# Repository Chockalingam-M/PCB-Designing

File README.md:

# PCB-Designing

🚀 Designed and developed this PCB as a demonstration of my skills in hardware design and precision layout. From component placement to trace optimization, every part of this board reflects my commitment to clean, functional, and professional electronic design.

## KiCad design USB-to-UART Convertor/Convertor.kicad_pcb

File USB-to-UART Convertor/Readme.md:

Overview
This project is a USB to UART bridge designed using the CH340K USB to Serial chip. It allows for easy communication between a computer and a microcontroller through a Type-C USB connector. 
Ideal for programming or debugging microcontrollers like ESP32, STM32, etc.

This USB to UART PCB was designed by carefully following Ampnics’ video and analyzing each functional block. While the current routing can be optimized further, 
The design serves its purpose effectively. Future revisions will focus on refining the layout, improving signal integrity, and enhancing grounding practices.

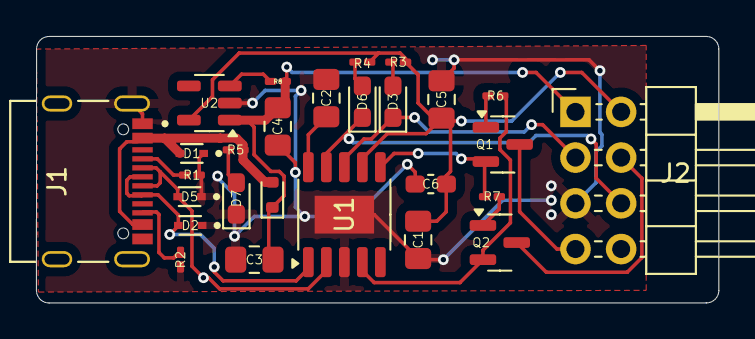
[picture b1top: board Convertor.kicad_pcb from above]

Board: 2 copper layers, 37.9 x 14.8 mm, 27 parts (0 on the bottom side), 21 nets.

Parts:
C1, C2: 100n; C_0805_2012Metric_Pad1.18x1.45mm_HandSolder
C3, C4, C5: 10u; C_0805_2012Metric_Pad1.18x1.45mm_HandSolder
C6: 0.1u; C_0603_1608Metric_Pad1.08x0.95mm_HandSolder
D1, D2, D5: LESD5D5.0CT1G; TVS_LESD5D5.0CT1G
D3, D6, D7: LED; LED_0603_1608Metric_Pad1.05x0.95mm_HandSolder
D4: D_Schottky; D_SOD-523
J1: USB_C_Receptacle_USB2.0_16P; HRO_TYPE-C-31-M-12
J2: Conn_02x04_Top_Bottom; PinHeader_2x04_P2.54mm_Horizontal
Q1, Q2: SS8050; SOT-23
R1, R2: 5.1k; R_0201_0603Metric_Pad0.64x0.40mm_HandSolder
R3, R4, R5: 220; R_0201_0603Metric_Pad0.64x0.40mm_HandSolder
R6, R7: 10k; R_0201_0603Metric_Pad0.64x0.40mm_HandSolder
R8: 100k; R_0201_0603Metric_Pad0.64x0.40mm_HandSolder
U1: CH340K; SSOP-10-1EP_3.9x4.9mm_P1mm_EP2.1x3.3mm
U2: AP2112K-3.3; SOT-23-5

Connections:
+3.3V: C1.1, C5.1, C6.1, J2.2, R3.1, R4.1, U1.7 (VCC), U2.5 (VOUT)
+5V: C3.1, C4.1, D4.1 (K), J2.1, R8.1, U2.1 (VIN)
D+: D2.2, J1.A6 (D+), J1.B6 (D+), U1.1 (UD+)
D-: D5.2, J1.A7 (D-), J1.B7 (D-), U1.2 (UD-)
DTR: Q2.2 (E), R6.1, U1.4 (~DTR)
EN: J2.7, Q1.3 (C)
GND: C1.2, C2.1, C3.2, C4.2, C5.2, C6.2, D1.1, D2.1, D5.1, D7.1 (K), J1.A12, J1.B12, J1.S1 (SHIELD), J2.5, R1.2, R2.2, U1.3 (GND), U1.11 (GND), U2.2 (GND)
IO0: J2.4, Q2.3 (C)
unnamed: D3.2 (A), R3.2
unnamed: D6.2 (A), R4.2
unnamed: D7.2 (A), R5.2
unnamed: J1.A5 (CC1), R1.1
unnamed: J1.B5 (CC2), R2.1
unnamed: Q1.1 (B), R6.2
unnamed: Q2.1 (B), R7.2
unnamed: C2.2, U1.10 (V3)
unnamed: R8.2, U2.3 (EN)
RTS: Q1.2 (E), R7.1, U1.6 (~RTS)
RXD: D3.1 (K), J2.3, U1.8 (TXD)
TXD: D6.1 (K), J2.6, U1.9 (RXD)
VBUS: D1.2, D4.2 (A), J1.A9, J1.B9, R5.1

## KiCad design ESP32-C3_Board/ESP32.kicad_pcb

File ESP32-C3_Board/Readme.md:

I’ve designed a PCB for the ESP32-C3 as my first hands-on attempt at circuit design using KiCad. This project helped me understand the complete workflow — from schematic creation to PCB layout. I followed along with a YouTube tutorial to guide the process and deepen my understanding of component placement, routing, and design rules.

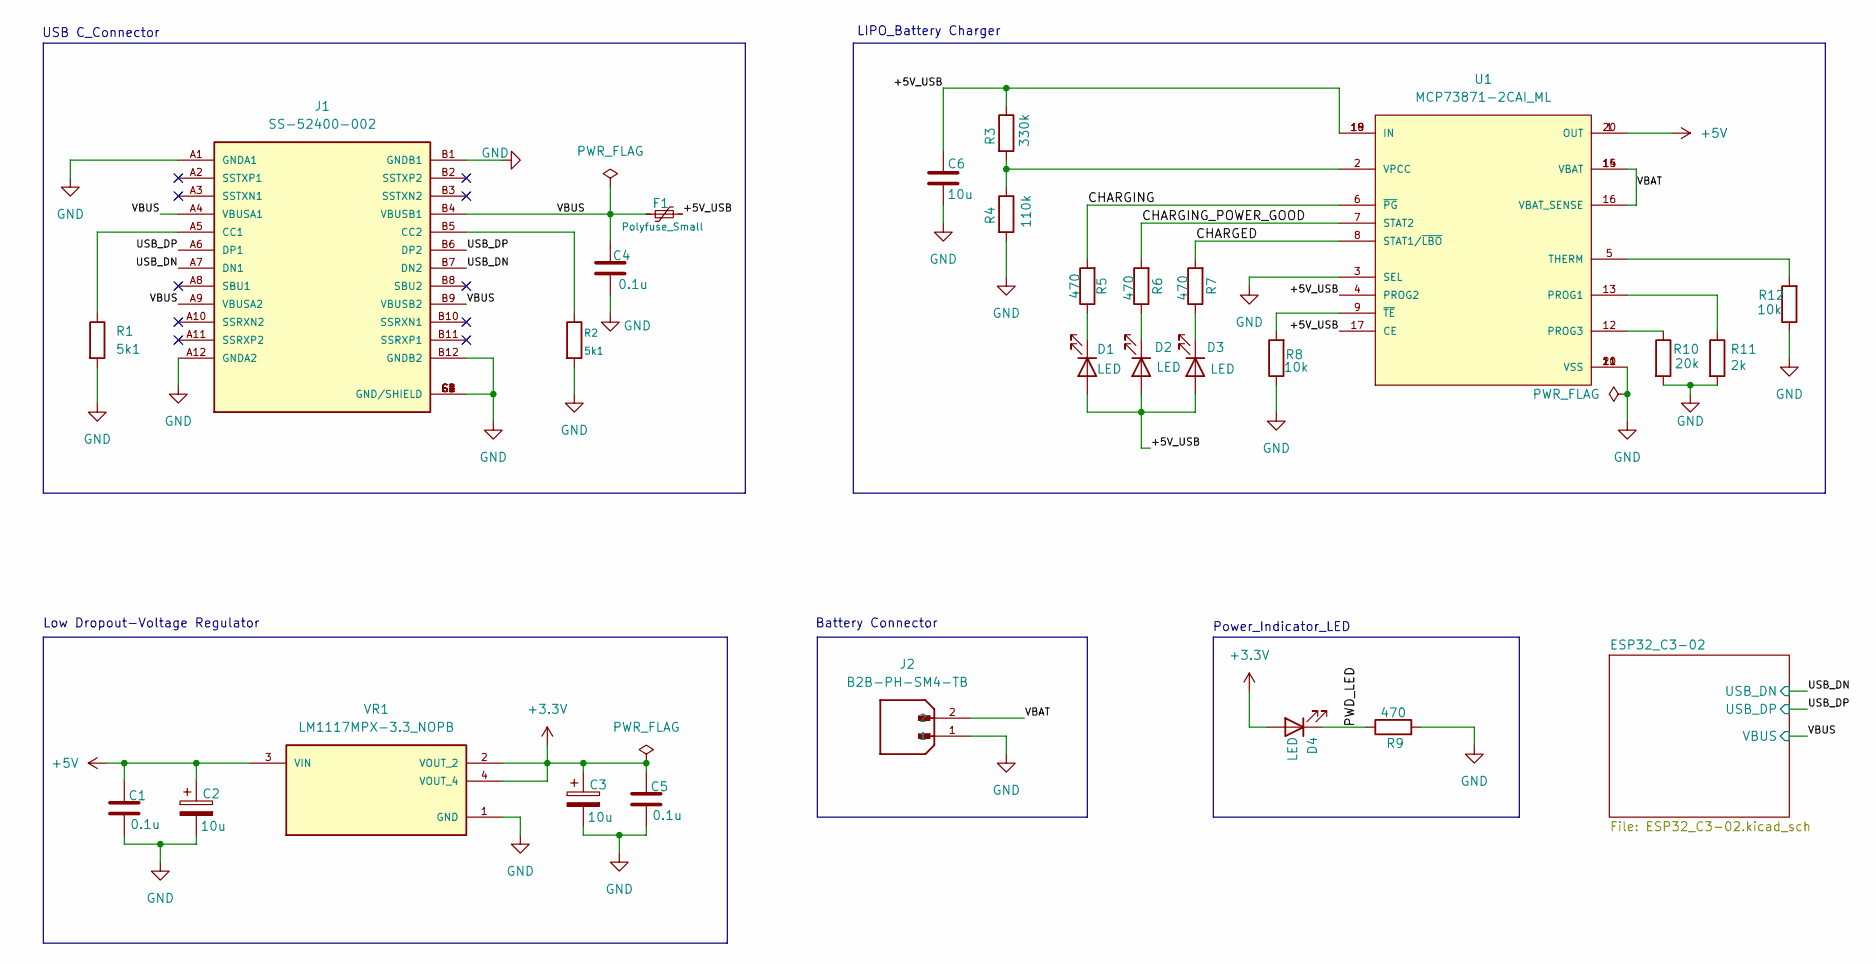
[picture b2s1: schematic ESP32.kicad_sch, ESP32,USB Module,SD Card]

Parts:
C1, C4, C5: 0.1u; C_0805_2012Metric
C2, C3, C6: 10u; CAPMP3216X180N
D1, D2, D3, D4: LED; LED_0805_2012Metric
F1: Polyfuse_Small; Fuse_0805_2012Metric
J1: SS-52400-002; BELFUSE_SS-52400-002; PARTREV A0
J2: B2B-PH-SM4-TB; JST_B2B-PH-SM4-TB; PARTREV N/A
R1, R2: 5k1; R_0805_2012Metric
R3: 330k; R_0805_2012Metric
R4: 110k; R_0805_2012Metric
R5, R6, R7, R9: 470; R_0805_2012Metric
R8, R12: 10k; R_0805_2012Metric
R10: 20k; R_0805_2012Metric
R11: 2k; R_0805_2012Metric
U1: MCP73871-2CAI_ML; QFN50P400X400X100-21N; PARTREV D
VR1: LM1117MPX-3.3_NOPB; VREG_LM1117MPX-3.3_NOPB; PARTREV O; DigiKey_Part_Number 488-LM1117MPX-33NOPBTR-ND

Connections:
+3.3V: C3.1, C5.1, D4.2 (A), VR1.2 (VOUT_2), VR1.4 (VOUT_4); also elsewhere on the board
+5V: C1.1, C2.1, U1.1 (OUT), U1.20 (OUT), VR1.3 (VIN)
/+5V_USB: C6.1, D1.2 (A), D2.2 (A), D3.2 (A), F1.2, R3.1, U1.4 (PROG2), U1.17 (CE), U1.18 (IN), U1.19 (IN)
/CHARGED: R7.2, U1.8 (STAT1/~LBO)
/CHARGING: R5.2, U1.6 (~PG)
/CHARGING_POWER_GOOD: R6.2, U1.7 (STAT2)
/PWD_LED: D4.1 (K), R9.1
/USB_DN: J1.A7 (DN1), J1.B7 (DN2); also elsewhere on the board
/USB_DP: J1.A6 (DP1), J1.B6 (DP2); also elsewhere on the board
/VBAT: J2.2, U1.14 (VBAT), U1.15 (VBAT), U1.16 (VBAT_SENSE)
/VBUS: C4.1, F1.1, J1.A4 (VBUSA1), J1.A9 (VBUSA2), J1.B4 (VBUSB1), J1.B9 (VBUSB2); also elsewhere on the board
GND: C1.2, C2.2, C3.2, C4.2, C5.2, C6.2, J1.A1 (GNDA1), J1.A12 (GNDA2), J1.B1 (GNDB1), J1.B12 (GNDB2), J1.G1 (GND/SHIELD), J1.G2 (GND/SHIELD), J1.G3 (GND/SHIELD), J1.G4 (GND/SHIELD), J1.S1 (GND/SHIELD), J1.S2 (GND/SHIELD), J1.S3 (GND/SHIELD), J1.S4 (GND/SHIELD), J2.1, R1.2, R2.2, R4.2, R8.1, R9.2, R10.2, R11.2, R12.1, U1.3 (SEL), U1.10 (VSS), U1.11 (VSS), U1.21 (VSS), VR1.1 (GND); also elsewhere on the board
unnamed: D1.1 (K), R5.1
unnamed: D2.1 (K), R6.1
unnamed: D3.1 (K), R7.1
unnamed: J1.A5 (CC1), R1.1
unnamed: J1.B5 (CC2), R2.1
unnamed: R11.1, U1.13 (PROG1)
unnamed: R10.1, U1.12 (PROG3)
unnamed: R12.2, U1.5 (THERM)
unnamed: R3.2, R4.1, U1.2 (VPCC)
unnamed: R8.2, U1.9 (~TE)

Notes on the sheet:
Low Dropout-Voltage Regulator
Battery Connector
Power_Indicator_LED
USB C_Connector
LIPO_Battery Charger

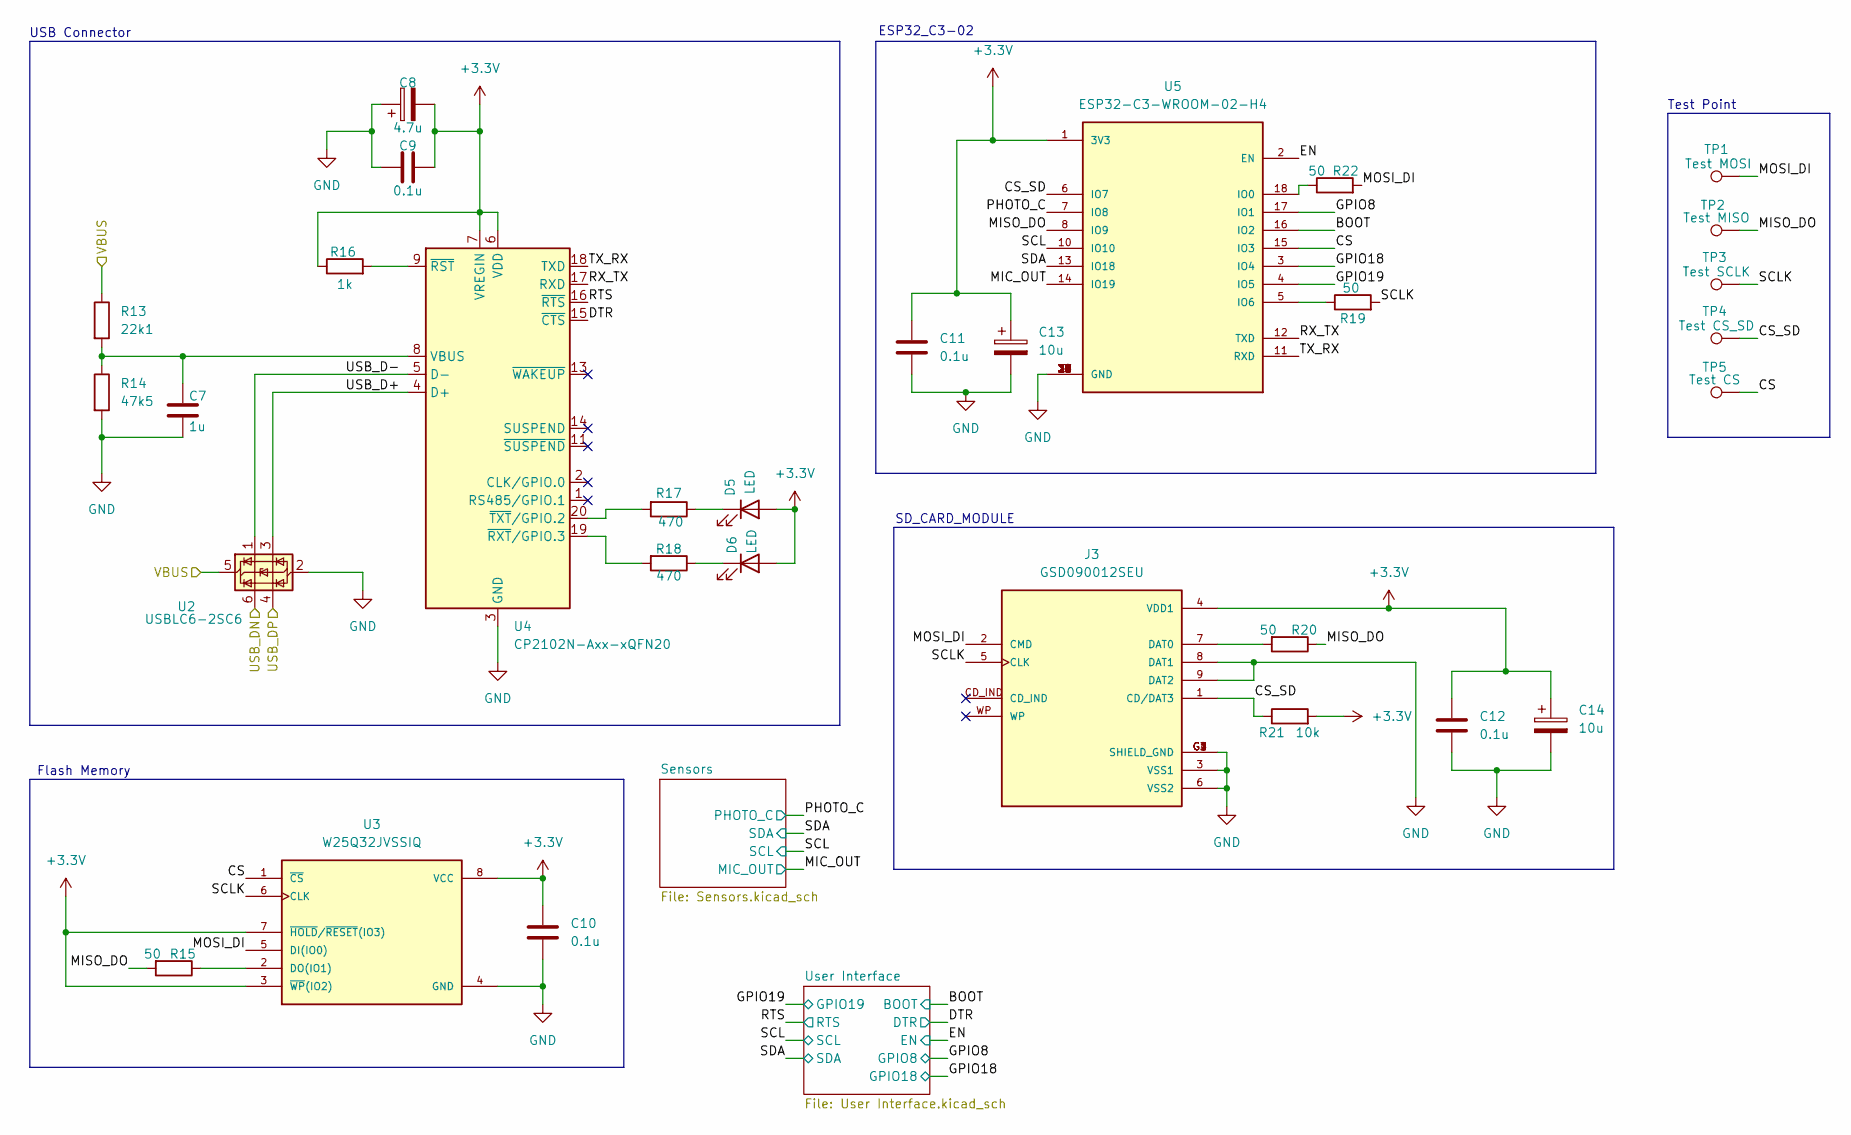
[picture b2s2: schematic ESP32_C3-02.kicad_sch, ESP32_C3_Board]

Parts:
C7: 1u; C_0805_2012Metric
C8: 4.7u; CAPMP3216X180N
C9, C10, C11, C12: 0.1u; C_0805_2012Metric
C13, C14: 10u; CAPMP3216X180N
D5, D6: LED; LED_0805_2012Metric
J3: GSD090012SEU; AMPHENOL_GSD090012SEU; PARTREV E
R13: 22k1; R_0805_2012Metric
R14: 47k5; R_0805_2012Metric
R15, R19, R20, R22: 50; R_0805_2012Metric
R16: 1k; R_0805_2012Metric
R17, R18: 470; R_0805_2012Metric
R21: 10k; R_0805_2012Metric
TP1: Test MOSI; TestPoint_Pad_D1.0mm
TP2: Test MISO; TestPoint_Pad_D1.0mm
TP3: Test SCLK; TestPoint_Pad_D1.0mm
TP4: Test CS_SD; TestPoint_Pad_D1.0mm
TP5: Test CS; TestPoint_Pad_D1.0mm
U2: USBLC6-2SC6; SOT-23-6
U3: W25Q32JVSSIQ; SOIC127P790X216-8N; M_PART_NUMBER W25QXX
U4: CP2102N-Axx-xQFN20; QFN50P400X400X100-21N
U5: ESP32-C3-WROOM-02-H4; MODULE_ESP32-C3-WROOM-02-H4

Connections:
+3.3V: C8.2, C9.2, C10.1, C11.1, C12.1, C13.1, C14.1, D5.2 (A), D6.2 (A), J3.4 (VDD1), R16.1, R21.2, U3.3 (~WP(IO2)), U3.7 (~HOLD/~RESET(IO3)), U3.8 (VCC), U4.6 (VDD), U4.7 (VREGIN), U5.1 (3V3); also elsewhere on the board
/ESP32_C3-02/BOOT: U5.16 (IO2); also elsewhere on the board
/ESP32_C3-02/CS: TP5.1, U3.1 (~CS), U5.15 (IO3)
/ESP32_C3-02/CS_SD: J3.1 (CD/DAT3), R21.1, TP4.1, U5.6 (IO7)
/ESP32_C3-02/DTR: U4.15 (~CTS); also elsewhere on the board
/ESP32_C3-02/EN: U5.2 (EN); also elsewhere on the board
/ESP32_C3-02/GPIO8: U5.17 (IO1); also elsewhere on the board
/ESP32_C3-02/GPIO18: U5.3 (IO4); also elsewhere on the board
/ESP32_C3-02/GPIO19: U5.4 (IO5); also elsewhere on the board
/ESP32_C3-02/MIC_OUT: U5.14 (IO19); also elsewhere on the board
/ESP32_C3-02/MISO_DO: R15.2, R20.1, TP2.1, U5.8 (IO9)
/ESP32_C3-02/MOSI_DI: J3.2 (CMD), R22.2, TP1.1, U3.5 (DI(IO0))
/ESP32_C3-02/PHOTO_C: U5.7 (IO8); also elsewhere on the board
/ESP32_C3-02/RTS: U4.16 (~RTS); also elsewhere on the board
/ESP32_C3-02/RX_TX: U4.17 (RXD), U5.12 (TXD)
/ESP32_C3-02/SCL: U5.10 (IO10); also elsewhere on the board
/ESP32_C3-02/SCLK: J3.5 (CLK), R19.2, TP3.1, U3.6 (CLK)
/ESP32_C3-02/SDA: U5.13 (IO18); also elsewhere on the board
/ESP32_C3-02/TX_RX: U4.18 (TXD), U5.11 (RXD)
/ESP32_C3-02/USB_D+: U2.3 (I/O2), U4.4 (D+)
/ESP32_C3-02/USB_D-: U2.1 (I/O1), U4.5 (D-)
/USB_DN: U2.6 (I/O1); also elsewhere on the board
/USB_DP: U2.4 (I/O2); also elsewhere on the board
/VBUS: R13.1, U2.5 (VBUS); also elsewhere on the board
GND: C7.2, C8.1, C9.1, C10.2, C11.2, C12.2, C13.2, C14.2, J3.3 (VSS1), J3.6 (VSS2), J3.8 (DAT1), J3.9 (DAT2), J3.G1 (SHIELD_GND), J3.G2 (SHIELD_GND), J3.G3 (SHIELD_GND), J3.G4 (SHIELD_GND), R14.2, U2.2 (GND), U3.4 (GND), U4.3 (GND), U4.12 (GND), U4.21 (GND), U5.9 (GND), U5.19 (GND), U5.20 (GND), U5.21 (GND), U5.22 (GND), U5.23 (GND), U5.24 (GND), U5.25 (GND), U5.26 (GND), U5.27 (GND), U5.28 (GND), U5.29 (GND), U5.30 (GND), U5.31 (GND), U5.32 (GND), U5.33 (GND), U5.34 (GND), U5.35 (GND), U5.36 (GND), U5.37 (GND), U5.38 (GND), U5.39 (GND); also elsewhere on the board
unnamed: D5.1 (K), R17.1
unnamed: D6.1 (K), R18.1
unnamed: J3.7 (DAT0), R20.2
unnamed: R15.1, U3.2 (DO(IO1))
unnamed: C7.1, R13.2, R14.1, U4.8 (VBUS)
unnamed: R16.2, U4.9 (~RST)
unnamed: R18.2, U4.19 (~RXT/GPIO.3)
unnamed: R17.2, U4.20 (~TXT/GPIO.2)
unnamed: R22.1, U5.18 (IO0)
unnamed: R19.1, U5.5 (IO6)

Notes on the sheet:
ESP32_C3-02
SD_CARD_MODULE
Test Point
USB Connector
Flash Memory

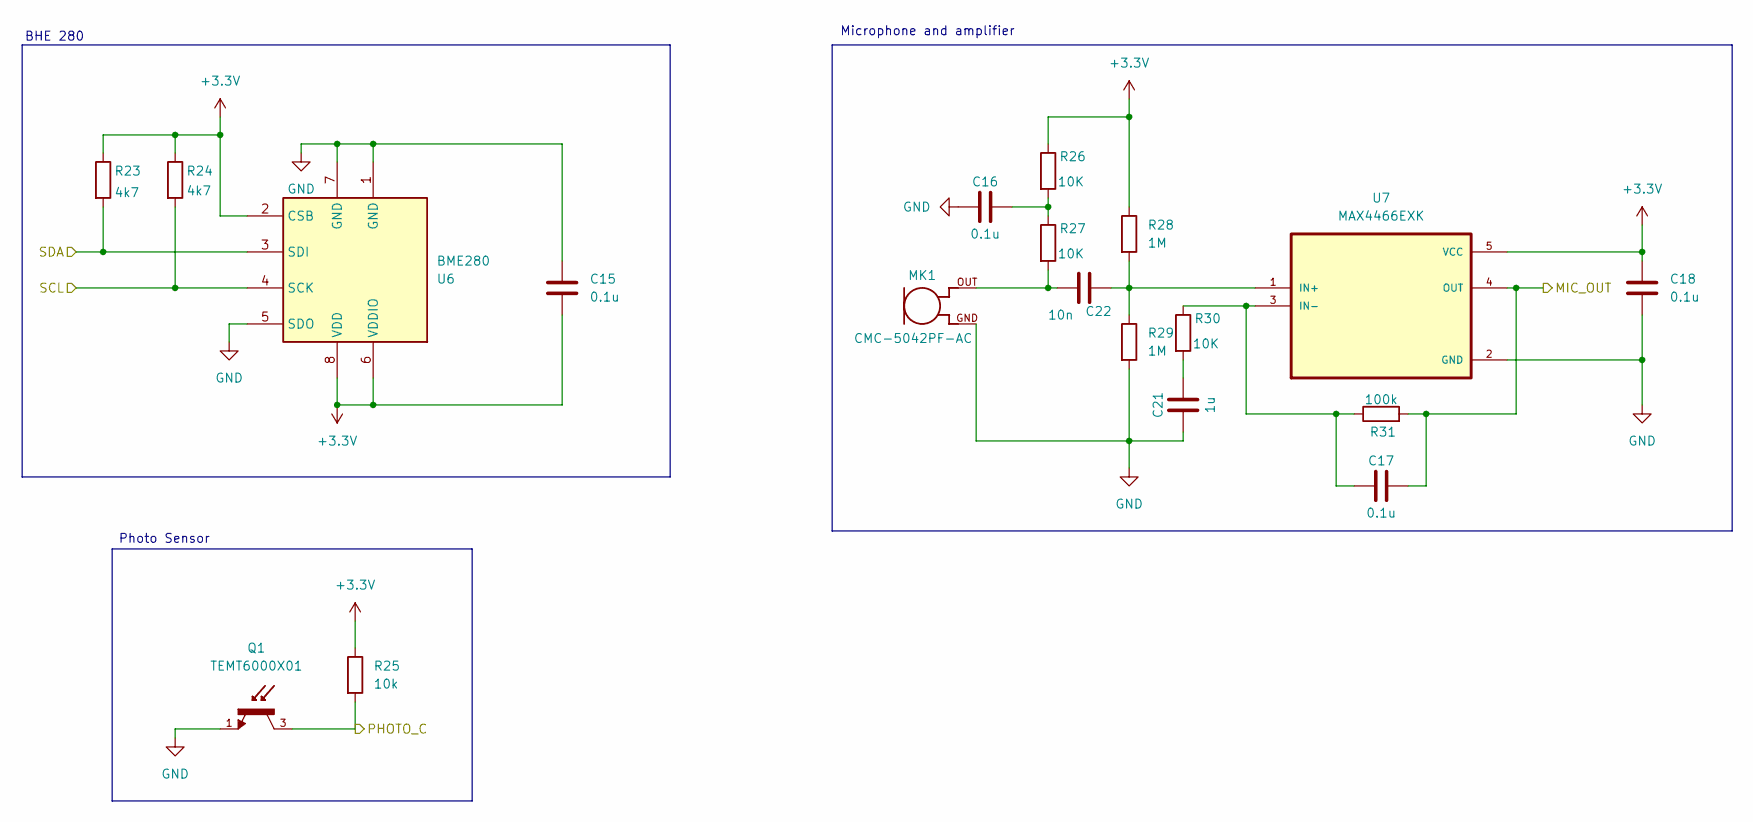
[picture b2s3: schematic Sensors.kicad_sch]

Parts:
C15, C16, C17, C18: 0.1u; C_0805_2012Metric
C21: 1u; C_0805_2012Metric
C22: 10n; C_0805_2012Metric
MK1: CMC-5042PF-AC; CUI_CMC-5042PF-AC
Q1: TEMT6000X01; TRANS_TEMT6000X01; PARTREV 1.9; DigiKey_Part_Number 751-1055-2-ND
R23, R24: 4k7; R_0805_2012Metric
R25: 10k; R_0805_2012Metric
R26, R27, R30: 10K; R_0805_2012Metric
R28, R29: 1M; R_0805_2012Metric
R31: 100k; R_0805_2012Metric
U6: BME280; Bosch_LGA-8_3x3mm_P0.8mm_ClockwisePinNumbering
U7: MAX4466EXK; SOT65P210X110-5N

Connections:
+3.3V: C15.2, C18.1, R23.1, R24.1, R25.1, R26.1, R28.1, U6.2 (CSB), U6.6 (VDDIO), U6.8 (VDD), U7.5 (VCC); also elsewhere on the board
/ESP32_C3-02/MIC_OUT: C17.2, R31.2, U7.4 (OUT); also elsewhere on the board
/ESP32_C3-02/PHOTO_C: Q1.3, R25.2; also elsewhere on the board
/ESP32_C3-02/SCL: R24.2, U6.4 (SCK); also elsewhere on the board
/ESP32_C3-02/SDA: R23.2, U6.3 (SDI); also elsewhere on the board
GND: C15.1, C16.1, C18.2, C21.1, MK1.GND, Q1.1, R29.2, U6.1 (GND), U6.5 (SDO), U6.7 (GND), U7.2 (GND); also elsewhere on the board
unnamed: C16.2, R26.2, R27.1
unnamed: C21.2, R30.2
unnamed: C22.2, MK1.OUT, R27.2
unnamed: C22.1, R28.2, R29.1, U7.1 (IN+)
unnamed: C17.1, R30.1, R31.1, U7.3 (IN-)

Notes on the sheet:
Microphone and amplifier
Photo Sensor
BHE 280

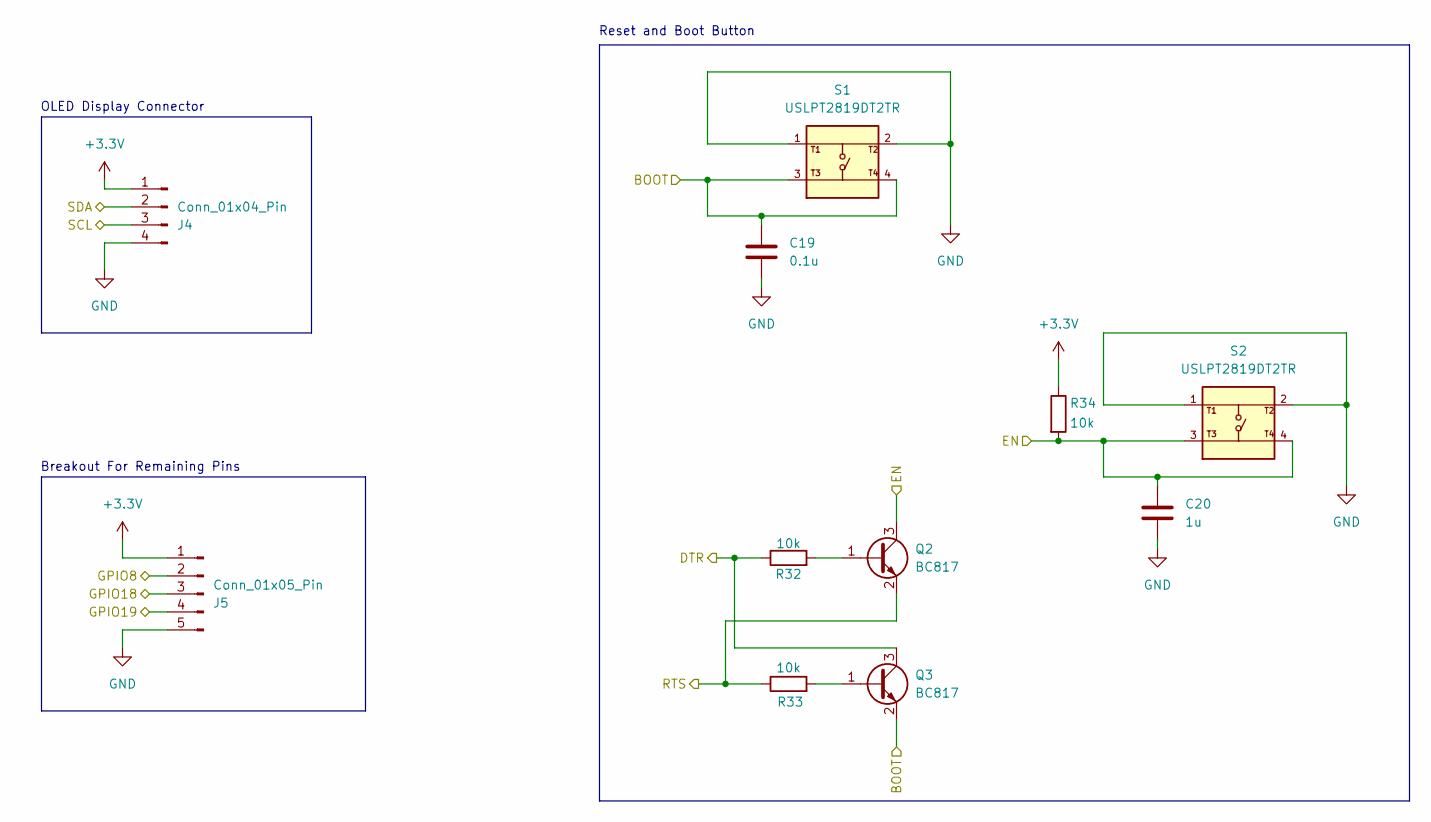
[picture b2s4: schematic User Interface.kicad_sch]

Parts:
C19: 0.1u; C_0805_2012Metric
C20: 1u; C_0805_2012Metric
J4: Conn_01x04_Pin; PinHeader_1x04_P2.54mm_Vertical
J5: Conn_01x05_Pin; PinHeader_1x05_P2.54mm_Vertical
Q2, Q3: BC817; SOT-23
R32, R33, R34: 10k; R_0805_2012Metric
S1, S2: USLPT2819DT2TR; SW_USLPT2819DT2TR; PARTREV P; DigiKey_Part_Number 450-3358-2-ND

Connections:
+3.3V: J4.1, J5.1, R34.1; also elsewhere on the board
/ESP32_C3-02/BOOT: C19.1, Q3.2 (E), S1.3, S1.4; also elsewhere on the board
/ESP32_C3-02/DTR: Q3.3 (C), R32.1; also elsewhere on the board
/ESP32_C3-02/EN: C20.1, Q2.3 (C), R34.2, S2.3, S2.4; also elsewhere on the board
/ESP32_C3-02/GPIO8: J5.2; also elsewhere on the board
/ESP32_C3-02/GPIO18: J5.3; also elsewhere on the board
/ESP32_C3-02/GPIO19: J5.4; also elsewhere on the board
/ESP32_C3-02/RTS: Q2.2 (E), R33.1; also elsewhere on the board
/ESP32_C3-02/SCL: J4.3; also elsewhere on the board
/ESP32_C3-02/SDA: J4.2; also elsewhere on the board
GND: C19.2, C20.2, J4.4, J5.5, S1.1, S1.2, S2.1, S2.2; also elsewhere on the board
unnamed: Q2.1 (B), R32.2
unnamed: Q3.1 (B), R33.2

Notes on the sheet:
Reset and Boot Button
Breakout For Remaining Pins
OLED Display Connector

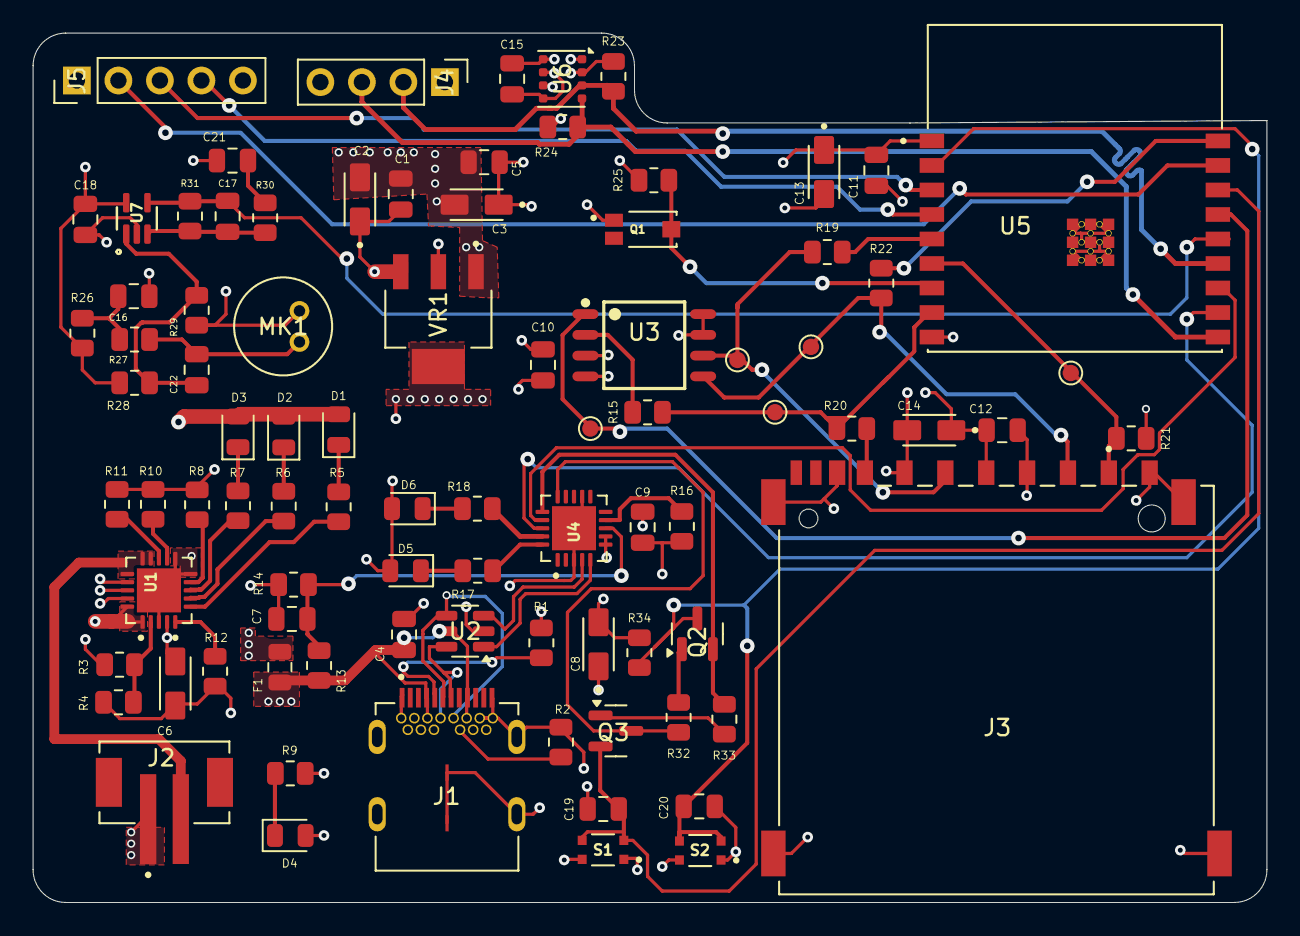
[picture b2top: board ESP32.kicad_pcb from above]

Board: 4 copper layers, 75.5 x 53.2 mm, 87 parts (0 on the bottom side), 59 nets.

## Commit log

2025-06-10 Create ESP3
2025-06-14 KICAD Files
